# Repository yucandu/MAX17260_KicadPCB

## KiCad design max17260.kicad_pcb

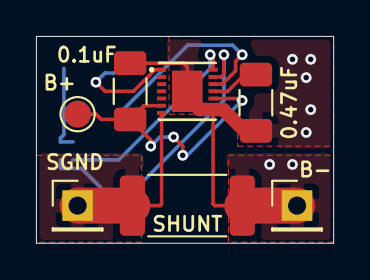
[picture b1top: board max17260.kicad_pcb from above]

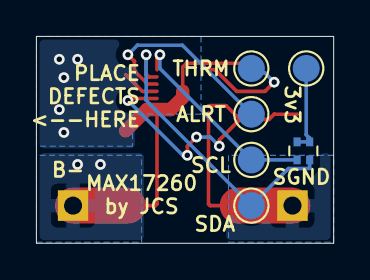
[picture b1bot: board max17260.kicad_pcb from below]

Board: 2 copper layers, 16.5 x 11.5 mm, 13 parts (6 on the bottom side), 9 nets.

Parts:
0.47uF: 0.47uF; C_1206_3216Metric_Pad1.33x1.80mm_HandSolder
3v3: TestPoint; TestPoint_Pad_D1.5mm
ALRT: TestPoint; TestPoint_Pad_D1.5mm
B+: TestPoint; TestPoint_Pad_D1.5mm
B-: TestPoint; PinHeader_1x01_P2.54mm_Vertical
C1: 0.1uF; C_1206_3216Metric_Pad1.33x1.80mm_HandSolder
RN1: 4k7; R_Array_Convex_2x0402
SCL: TestPoint; TestPoint_Pad_D1.5mm
SDA: TestPoint; TestPoint_Pad_D1.5mm
SGND: TestPoint; PinHeader_1x01_P2.54mm_Vertical
SHUNT: RSense; R_2512_6332Metric_Pad1.40x3.35mm_HandSolder
THRM: THERM; TestPoint_Pad_D1.5mm
U1: MAX17260SETD+T; TDFN-14_L3.0-W3.0-P0.40-BL-EP

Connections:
+BATT: B+.1 (1_1), C1.1, U1.6 (BATT), U1.10 (CSPH)
-BATT: 0.47uF.2, B-.1 (1_1), C1.2, SHUNT.1, U1.8 (GND), U1.9 (CSPL), U1.15 (EP)
GNDS: SGND.1 (1_1), SHUNT.2, U1.7 (CSN)
unnamed: RN1.1 (R1.1), SCL.1 (1_1), U1.14 (SCL)
unnamed: 3v3.1 (1_1), RN1.3 (R2.2), RN1.4 (R1.2)
unnamed: RN1.2 (R2.1), SDA.1 (1_1), U1.13 (SDA)
unnamed: ALRT.1 (1_1), U1.12 (ALRT)
unnamed: 0.47uF.1, U1.11 (REG)
unnamed: THRM.1 (1_1), U1.1 (TH)
